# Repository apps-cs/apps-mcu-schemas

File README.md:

# K64F-KIT and Extension Modules

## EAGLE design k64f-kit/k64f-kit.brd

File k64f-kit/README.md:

# Base module K64F-KIT

The base module with ZIF sockets.

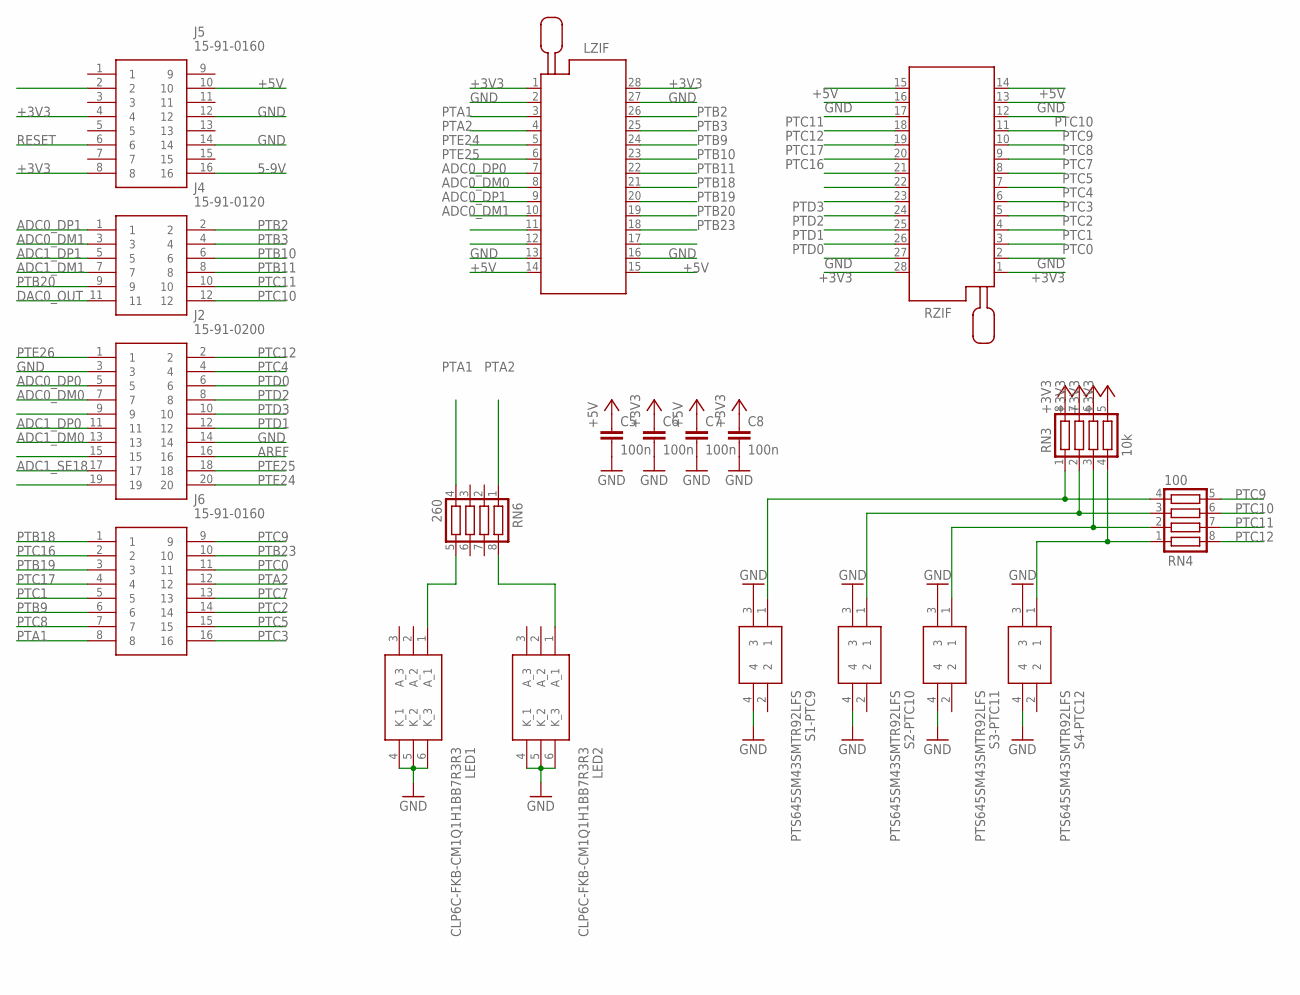
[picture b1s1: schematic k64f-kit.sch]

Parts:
C5, C6, C7, C8: 100n; C1206
J2: 15-91-0200; 15910200
J4: 15-91-0120; 15910120
J5, J6: 15-91-0160; 15910160
LED1, LED2: CLP6C-FKB-CM1Q1H1BB7R3R3; CLP6CFKBCM1Q1H1BB7R3R3
LZIF: 228-22-602; 228-1277-00-0602J
RN3: 10k; CTS742C083; FARNELL 1770137
RN4: 100; CTS742C083; FARNELL 1770131
RN6: 260; CTS742C083; FARNELL 2908182
RZIF: 228-22-602; 228-1277-00-0602J
S1-PTC9, S2-PTC10, S3-PTC11, S4-PTC12: PTS645SM43SMTR92LFS; PTS645(SMT); FARNELL 2320087

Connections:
5-9V: J5.16
+3V3: C6.1, C8.1, J5.4, J5.8, LZIF.1, LZIF.28, RN3.5, RN3.6, RN3.7, RN3.8, RZIF.1, RZIF.28
+5V: C5.1, C7.1, J5.10, LZIF.14, LZIF.15, RZIF.14, RZIF.15
ADC0_DM0: J2.7, LZIF.8
ADC0_DM1: J4.3, LZIF.10
ADC0_DP0: J2.5, LZIF.7
ADC0_DP1: J4.1, LZIF.9
ADC1_DM0: J2.13
ADC1_DM1: J4.7
ADC1_DP0: J2.11
ADC1_DP1: J4.5
ADC1_SE18: J2.17
AREF: J2.16
DAC0_OUT: J4.11
GND: C5.2, C6.2, C7.2, C8.2, J2.3, J2.14, J5.12, J5.14, LED1.4 (K_1), LED1.5 (K_2), LED1.6 (K_3), LED2.4 (K_1), LED2.5 (K_2), LED2.6 (K_3), LZIF.2, LZIF.13, LZIF.16, LZIF.27, RZIF.2, RZIF.13, RZIF.16, RZIF.27, S1-PTC9.3, S1-PTC9.4, S2-PTC10.3, S2-PTC10.4, S3-PTC11.3, S3-PTC11.4, S4-PTC12.3, S4-PTC12.4
unnamed: RN3.1, RN4.4, S1-PTC9.1
unnamed: RN3.2, RN4.3, S2-PTC10.1
unnamed: RN3.3, RN4.2, S3-PTC11.1
unnamed: RN3.4, RN4.1, S4-PTC12.1
unnamed: LED2.1 (A_1), RN6.8
unnamed: LED1.1 (A_1), RN6.5
PTA1: J6.8, LZIF.3, RN6.1
PTA2: J6.12, LZIF.4, RN6.4
PTB2: J4.2, LZIF.26
PTB3: J4.4, LZIF.25
PTB9: J6.6, LZIF.24
PTB10: J4.6, LZIF.23
PTB11: J4.8, LZIF.22
PTB18: J6.1, LZIF.21
PTB19: J6.3, LZIF.20
PTB20: J4.9, LZIF.19
PTB23: J6.10, LZIF.18
PTC0: J6.11, RZIF.3
PTC1: J6.5, RZIF.4
PTC2: J6.14, RZIF.5
PTC3: J6.16, RZIF.6
PTC4: J2.4, RZIF.7
PTC5: J6.15, RZIF.8
PTC7: J6.13, RZIF.9
PTC8: J6.7, RZIF.10
PTC9: J6.9, RN4.5, RZIF.11
PTC10: J4.12, RN4.6, RZIF.12
PTC11: J4.10, RN4.7, RZIF.17
PTC12: J2.2, RN4.8, RZIF.18
PTC16: J6.2, RZIF.20
PTC17: J6.4, RZIF.19
PTD0: J2.6, RZIF.26
PTD1: J2.12, RZIF.25
PTD2: J2.8, RZIF.24
PTD3: J2.10, RZIF.23
PTE24: J2.20, LZIF.5
PTE25: J2.18, LZIF.6
PTE26: J2.1
RESET: J5.6

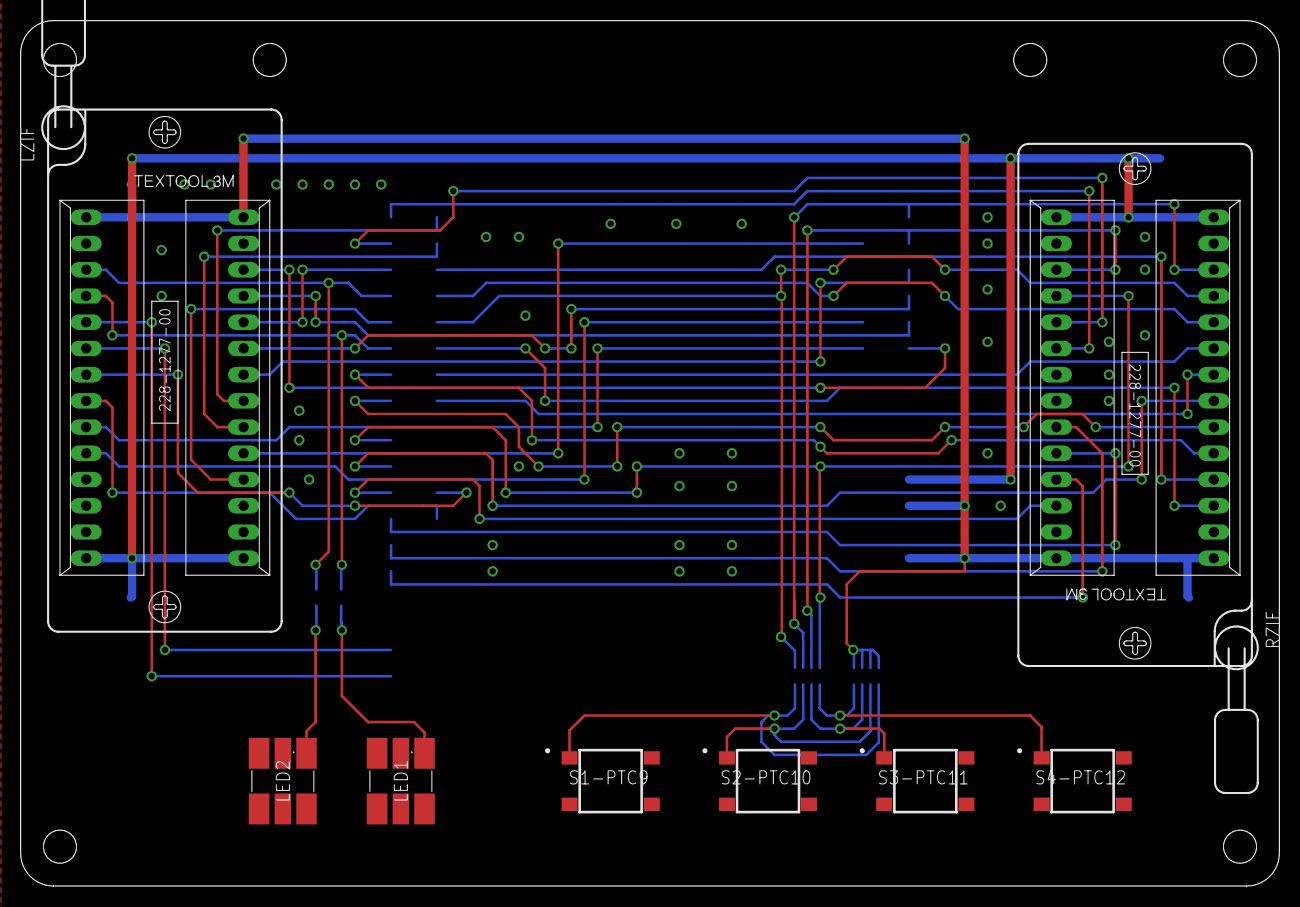
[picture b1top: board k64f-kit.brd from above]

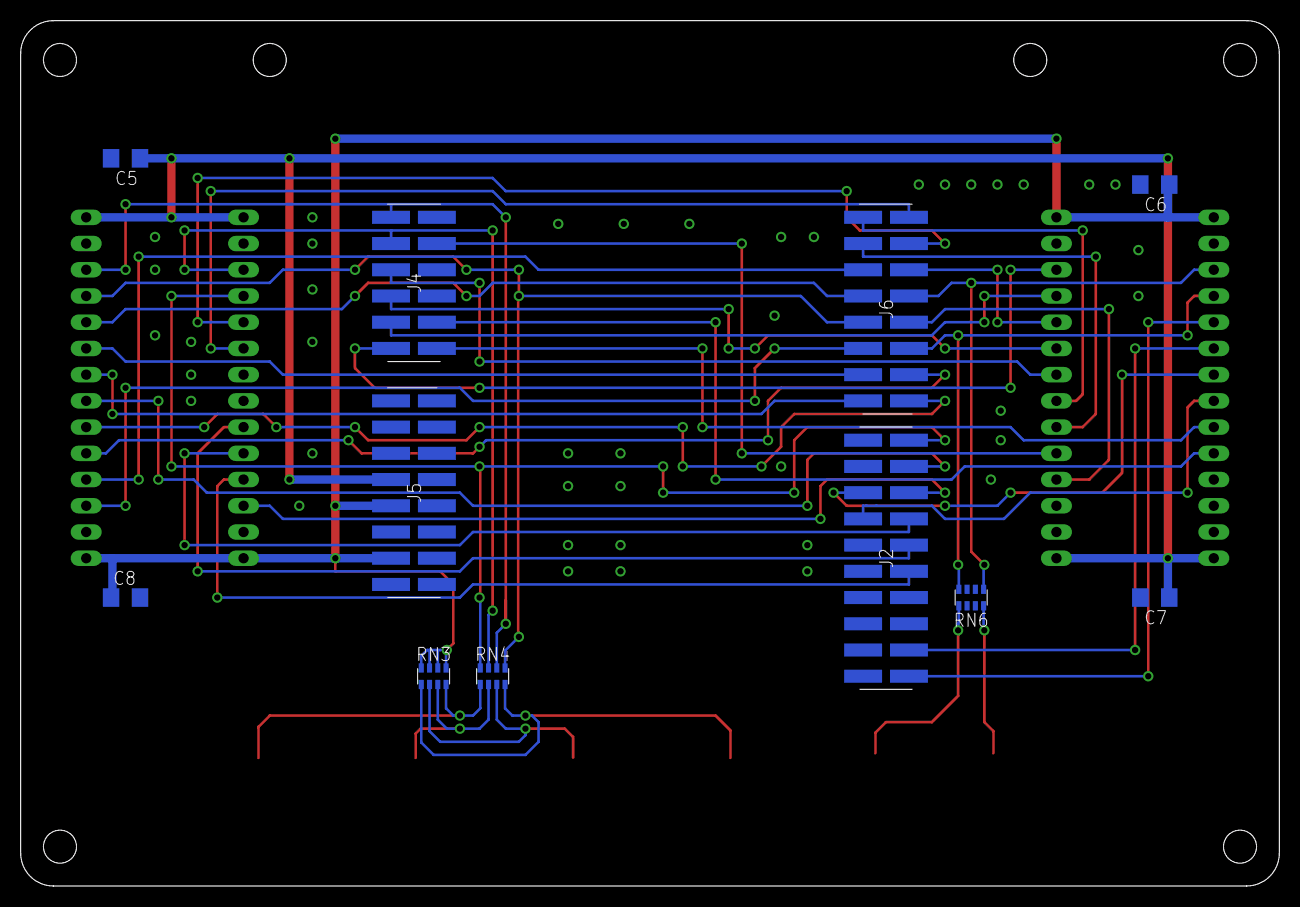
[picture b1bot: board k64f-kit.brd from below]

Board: 2 copper layers, 121.9 x 83.8 mm, 19 parts (11 on the bottom side), 44 nets.

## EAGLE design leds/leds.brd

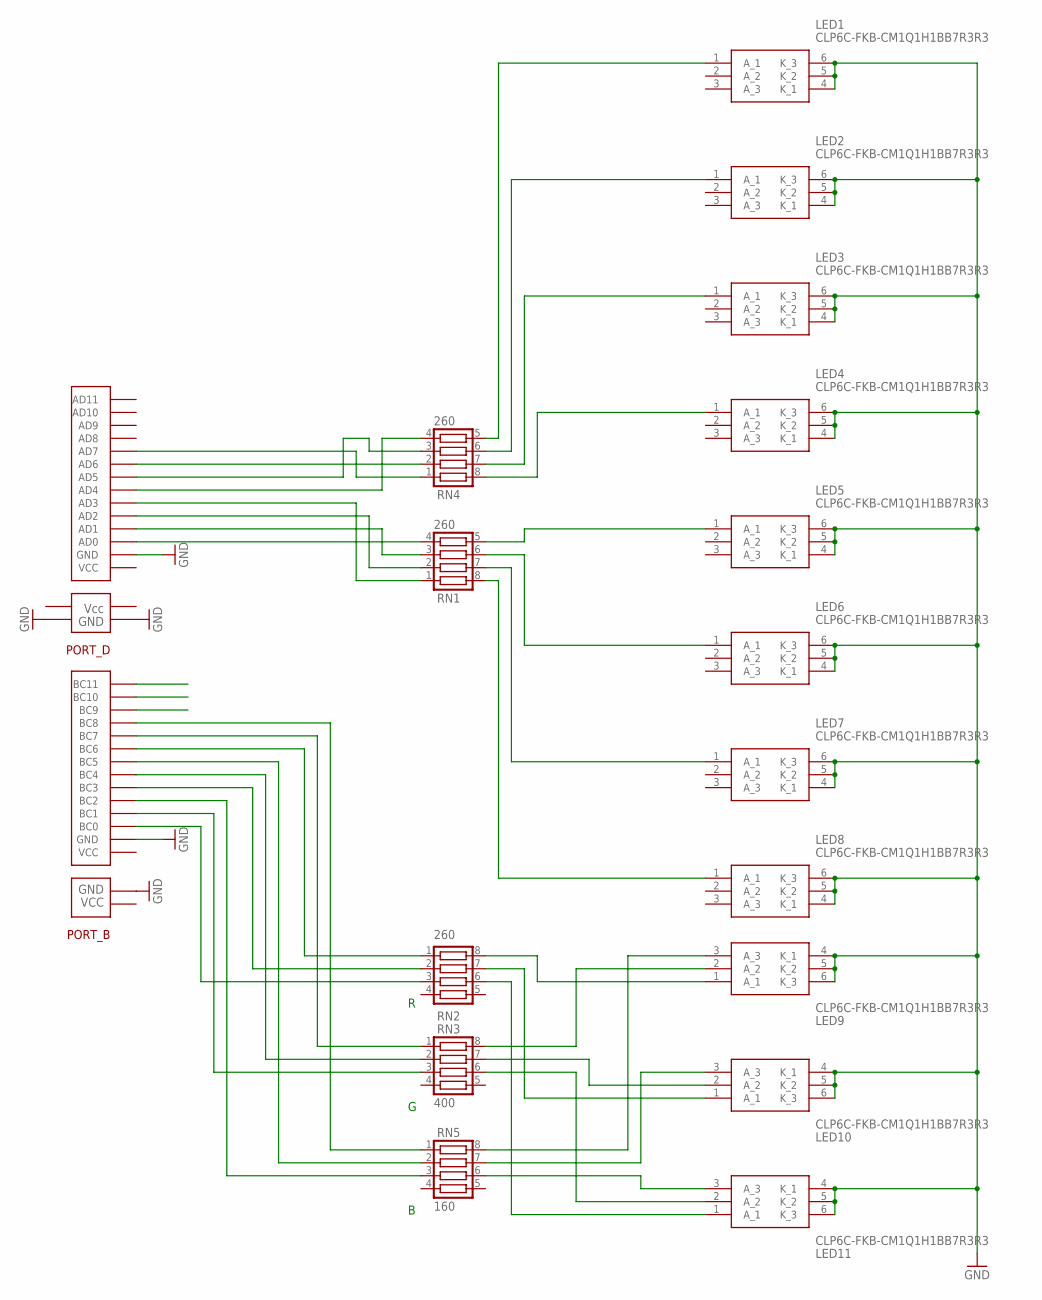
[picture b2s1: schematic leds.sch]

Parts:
LED1, LED2, LED3, LED4, LED5, LED6, LED7, LED8, LED9, LED10, LED11: CLP6C-FKB-CM1Q1H1BB7R3R3; CLP6CFKBCM1Q1H1BB7R3R3
PORT_B: PATICE_CERVENA
PORT_D: PATICE_ZELENA
RN1, RN2, RN4: 260; CTS742C083; FARNELL 2908182
RN3: 400; CTS742C083; FARNELL 2787792
RN5: 160; CTS742C083; FARNELL 2321721

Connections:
GND: LED1.4 (K_1), LED1.5 (K_2), LED1.6 (K_3), LED2.4 (K_1), LED2.5 (K_2), LED2.6 (K_3), LED3.4 (K_1), LED3.5 (K_2), LED3.6 (K_3), LED4.4 (K_1), LED4.5 (K_2), LED4.6 (K_3), LED5.4 (K_1), LED5.5 (K_2), LED5.6 (K_3), LED6.4 (K_1), LED6.5 (K_2), LED6.6 (K_3), LED7.4 (K_1), LED7.5 (K_2), LED7.6 (K_3), LED8.4 (K_1), LED8.5 (K_2), LED8.6 (K_3), LED9.4 (K_1), LED9.5 (K_2), LED9.6 (K_3), LED10.4 (K_1), LED10.5 (K_2), LED10.6 (K_3), LED11.4 (K_1), LED11.5 (K_2), LED11.6 (K_3), PORT_B.GND, PORT_B.GND/ (GND), PORT_D.GND, PORT_D.GND/ (GND), PORT_D.GND// (GND)
unnamed: LED1.1 (A_1), RN4.5
unnamed: LED2.1 (A_1), RN4.6
unnamed: LED3.1 (A_1), RN4.7
unnamed: LED4.1 (A_1), RN4.8
unnamed: PORT_B.CB3 (BC3), RN2.2
unnamed: PORT_B.CB0 (BC0), RN2.3
unnamed: LED7.1 (A_1), RN1.7
unnamed: LED9.2 (A_2), RN3.8
unnamed: LED8.1 (A_1), RN1.8
unnamed: PORT_D.AD0, RN1.4
unnamed: PORT_B.CB6 (BC6), RN2.1
unnamed: PORT_D.AD1, RN1.3
unnamed: PORT_B.CB2 (BC2), RN5.3
unnamed: PORT_D.AD2, RN1.2
unnamed: PORT_D.AD3, RN1.1
unnamed: PORT_D.AD7, RN4.1
unnamed: PORT_D.AD6, RN4.2
unnamed: PORT_D.AD5, RN4.3
unnamed: PORT_D.AD4, RN4.4
unnamed: LED5.1 (A_1), RN1.5
unnamed: PORT_B.CB1 (BC1), RN3.3
unnamed: PORT_B.CB7 (BC7), RN3.1
unnamed: LED6.1 (A_1), RN1.6
unnamed: PORT_B.CB8 (BC8), RN5.1
unnamed: PORT_B.CB5 (BC5), RN5.2
unnamed: PORT_B.CB4 (BC4), RN3.2
unnamed: LED9.3 (A_3), RN5.8
unnamed: LED10.3 (A_3), RN5.7
unnamed: LED11.3 (A_3), RN5.6
unnamed: LED9.1 (A_1), RN2.8
unnamed: LED10.1 (A_1), RN2.7
unnamed: LED11.1 (A_1), RN2.6
unnamed: LED11.2 (A_2), RN3.6
unnamed: LED10.2 (A_2), RN3.7

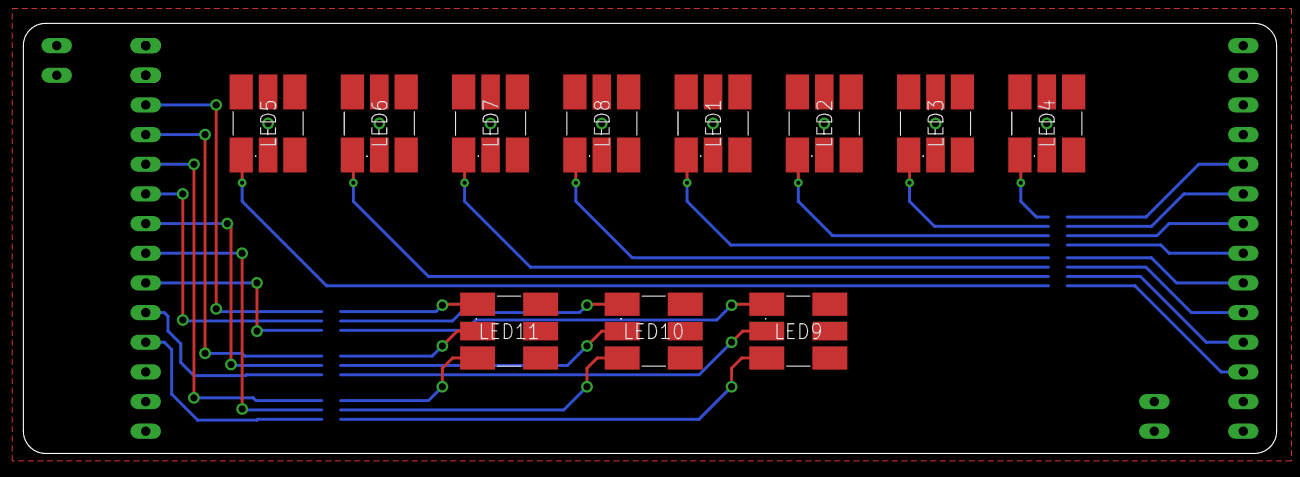
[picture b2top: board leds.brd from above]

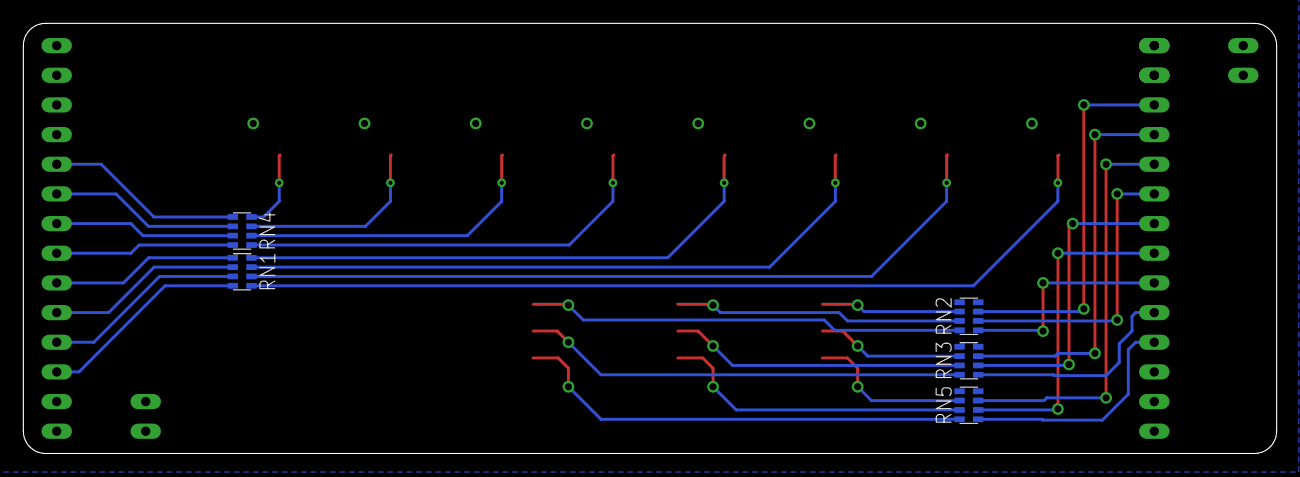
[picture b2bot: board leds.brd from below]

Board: 2 copper layers, 107.3 x 36.8 mm, 18 parts (5 on the bottom side), 35 nets.

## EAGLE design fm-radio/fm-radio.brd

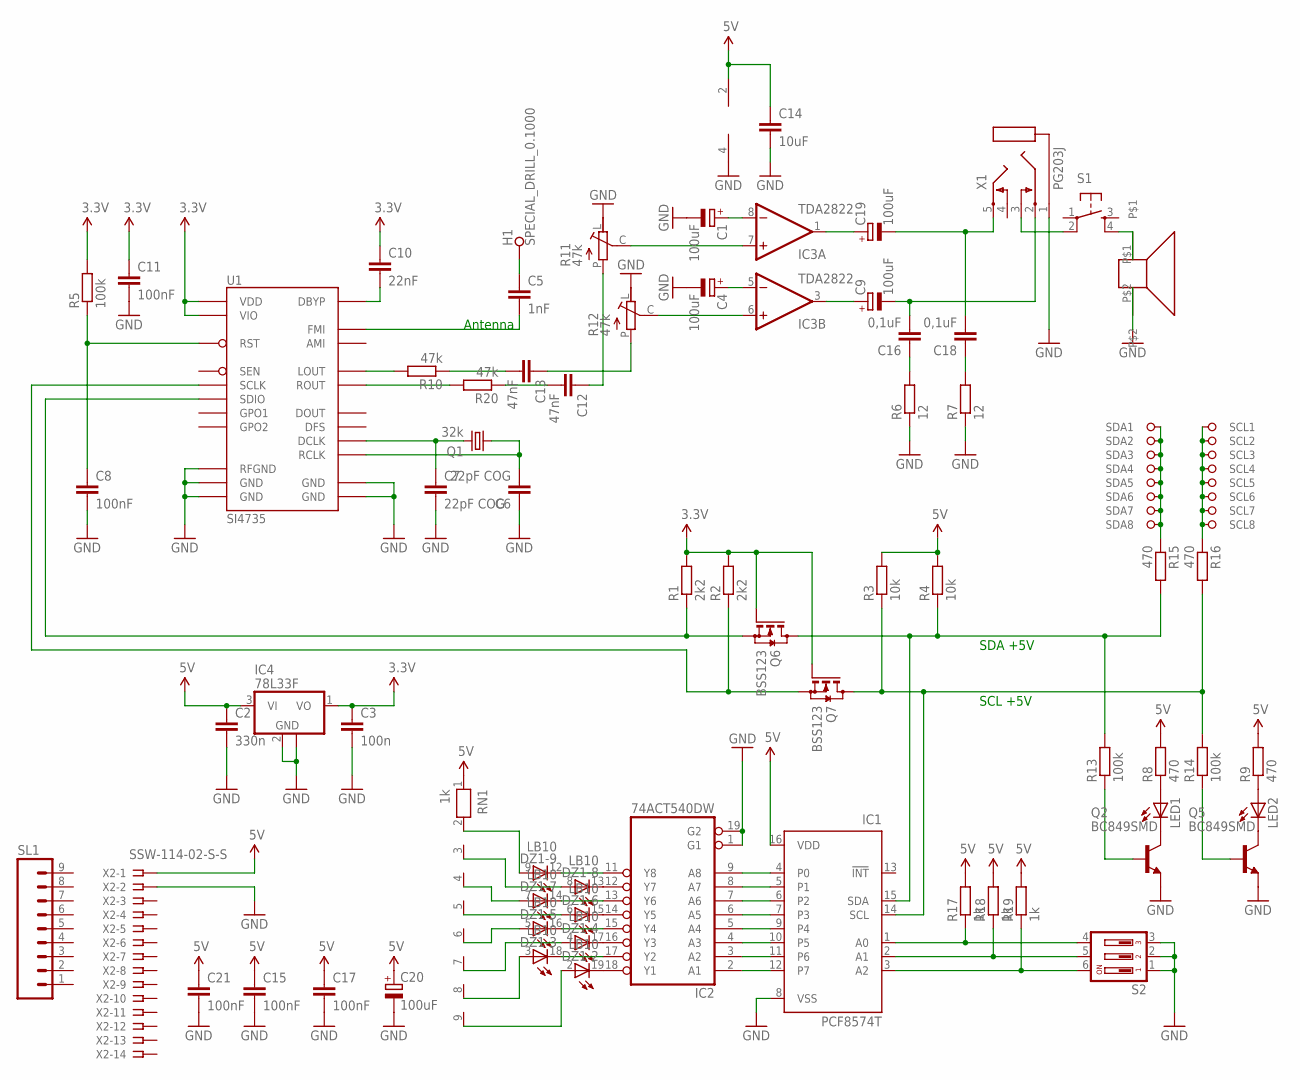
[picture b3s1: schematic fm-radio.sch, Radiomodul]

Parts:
C1, C4, C9, C19, C20: 100uF; CT3528
C2: 330n; C1206
C3: 100n; C1206
C5: 1nF; C1206
C6, C7: 22pF COG; C1206
C8, C11, C15, C17, C21: 100nF; C1206
C10: 22nF; C1206
C12, C13: 47nF; C1206
C14: 10uF; C1206
C16, C18: 0,1uF; C1206
DZ1: LB10
H1: SPECIAL_DRILL_0.1000; PAD_0.1000
IC1: PCF8574T; SO16W
IC2: 74ACT540DW; SO20W
IC3: TDA2822; SO08
IC4: 78L33F; SOT89
LED1, LED2: LEDCHIPLED_1206; CHIPLED_1206
Q1: 32k; MC-306
Q2, Q5: BC849SMD; SOT23-BEC
Q6, Q7: BSS123; SOT23
R1, R2: 2k2; R1206
R3, R4: 10k; R1206
R5, R13, R14: 100k; R1206
R6, R7: 12; R1206
R8, R9, R15, R16: 470; R1206
R10, R20: 47k; R1206
R11, R12: 47k; TRIMER
R17, R18, R19: 1k; R1206
RN1: 1k; RN-9
S1: TAC_SWITCHPTH; TACTILE-PTH
S2: DIP03YL
SL1: M09; 09P
U1: SI4735; SSOP24_NARROW
U$1: K23PC
U$7: PATICE_I2C
X1: PG203J
X2: SSW-114-02-S-S

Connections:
3.3V: C3.1, C10.1, C11.1, IC4.1 (VO), Q6.1 (G), Q7.1 (G), R1.2, R2.2, R5.2, U1.20 (VIO), U1.21 (VDD)
5V: C2.1, C14.1, C15.1, C17.1, C20.+, C21.1, IC1.16 (VDD), IC3.2 (V+), IC4.3 (VI), R3.2, R4.2, R8.2, R9.2, R17.2, R18.2, R19.2, RN1.1, X2.1
GND: C1.-, C2.2, C3.2, C4.-, C6.1, C7.2, C8.2, C11.2, C14.2, C15.2, C17.2, C20.-, C21.2, IC1.8 (VSS), IC2.1 (G1), IC2.10 (GND), IC2.19 (G2), IC3.4 (GND), IC4.2 (GND), IC4.2@1 (GND), Q2.E, Q5.E, R6.1, R7.1, R11.L, R12.L, S2.1, S2.2, S2.3, U1.9 (RFGND), U1.10 (GND), U1.11 (GND), U1.13 (GND), U1.14 (GND), U$1.P$2, X1.1, X2.2
unnamed: IC1.15 (SDA), Q6.3 (D), R4.1, R13.2, R15.2
unnamed: R16.1, U$7.SCL_1 (SCL1), U$7.SCL_2 (SCL2), U$7.SCL_3 (SCL3), U$7.SCL_4 (SCL4), U$7.SCL_5 (SCL5), U$7.SCL_6 (SCL6), U$7.SCL_7 (SCL7), U$7.SCL_8 (SCL8)
unnamed: Q7.2 (S), R2.1, U1.17 (SCLK)
unnamed: IC3.7 (+IN), R11.C
unnamed: Q6.2 (S), R1.1, U1.18 (SDIO)
unnamed: C5.2, U1.8 (FMI)
unnamed: C5.1, H1.1
unnamed: C7.1, Q1.4 (2), U1.3 (DCLK)
unnamed: C13.1, R12.P
unnamed: C8.1, R5.1, U1.15 (RST)
unnamed: S1.2, X1.3
unnamed: C1.+, IC3.8 (-IN)
unnamed: C6.2, Q1.1, U1.19 (RCLK)
unnamed: C10.2, U1.22 (DBYP)
unnamed: C12.1, R11.P
unnamed: S1.4, U$1.P$1
unnamed: C4.+, IC3.5 (-IN)
unnamed: IC3.6 (+IN), R12.C
unnamed: C16.1, R6.2
unnamed: C9.-, C16.2, X1.2
unnamed: C18.1, R7.2
unnamed: C18.2, C19.-, X1.5
unnamed: C19.+, IC3.1 (OUT)
unnamed: C9.+, IC3.3 (OUT)
unnamed: LED1.C, Q2.C
unnamed: LED2.C, Q5.C
unnamed: LED1.A, R8.1
unnamed: LED2.A, R9.1
unnamed: Q2.B, R13.1
unnamed: Q5.B, R14.1
unnamed: R15.1, U$7.SDA_1 (SDA1), U$7.SDA_2 (SDA2), U$7.SDA_3 (SDA3), U$7.SDA_4 (SDA4), U$7.SDA_5 (SDA5), U$7.SDA_6 (SDA6), U$7.SDA_7 (SDA7), U$7.SDA_8 (SDA8)
unnamed: IC1.14 (SCL), Q7.3 (D), R3.1, R14.2, R16.2
unnamed: IC1.4 (P0), IC2.9 (A8)
unnamed: IC1.12 (P7), IC2.2 (A1)
unnamed: IC1.11 (P6), IC2.3 (A2)
unnamed: IC1.10 (P5), IC2.4 (A3)
unnamed: IC1.9 (P4), IC2.5 (A4)
unnamed: IC1.7 (P3), IC2.6 (A5)
unnamed: IC1.6 (P2), IC2.7 (A6)
unnamed: IC1.5 (P1), IC2.8 (A7)
unnamed: DZ1.12 (C), IC2.11 (Y8)
unnamed: DZ1.13 (C), IC2.12 (Y7)
unnamed: DZ1.14 (C), IC2.13 (Y6)
unnamed: DZ1.15 (C), IC2.14 (Y5)
unnamed: DZ1.16 (C), IC2.15 (Y4)
unnamed: DZ1.17 (C), IC2.16 (Y3)
unnamed: DZ1.18 (C), IC2.17 (Y2)
unnamed: DZ1.19 (C), IC2.18 (Y1)
unnamed: DZ1.9 (A), RN1.2
unnamed: DZ1.8 (A), RN1.3
unnamed: DZ1.7 (A), RN1.4
unnamed: DZ1.6 (A), RN1.5
unnamed: DZ1.5 (A), RN1.6
unnamed: DZ1.4 (A), RN1.7
unnamed: DZ1.3 (A), RN1.8
unnamed: DZ1.2 (A), RN1.9
unnamed: IC1.1 (A0), R17.1, S2.4
unnamed: IC1.2 (A1), R18.1, S2.5
unnamed: IC1.3 (A2), R19.1, S2.6
unnamed: R10.2, U1.24 (LOUT)
unnamed: C12.2, R20.1
unnamed: C13.2, R10.1
unnamed: R20.2, U1.23 (ROUT)
VCC: IC2.20 (VCC)

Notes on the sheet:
SDA +5V
SCL +5V
Antenna

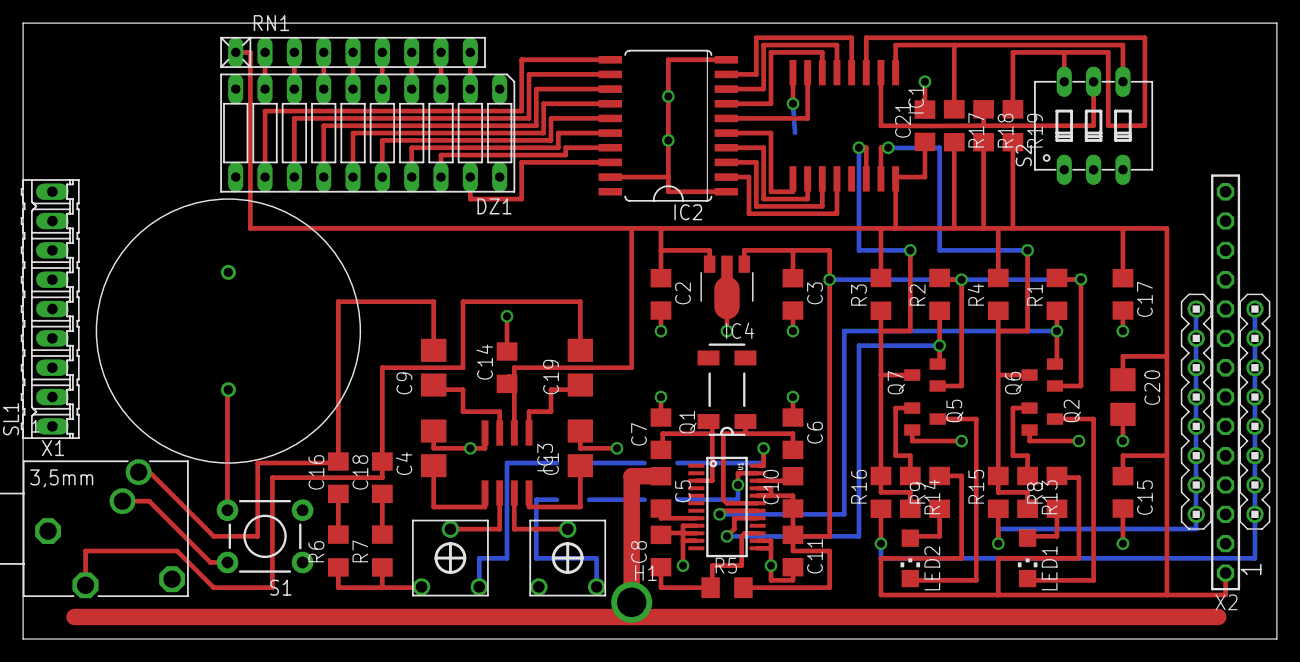
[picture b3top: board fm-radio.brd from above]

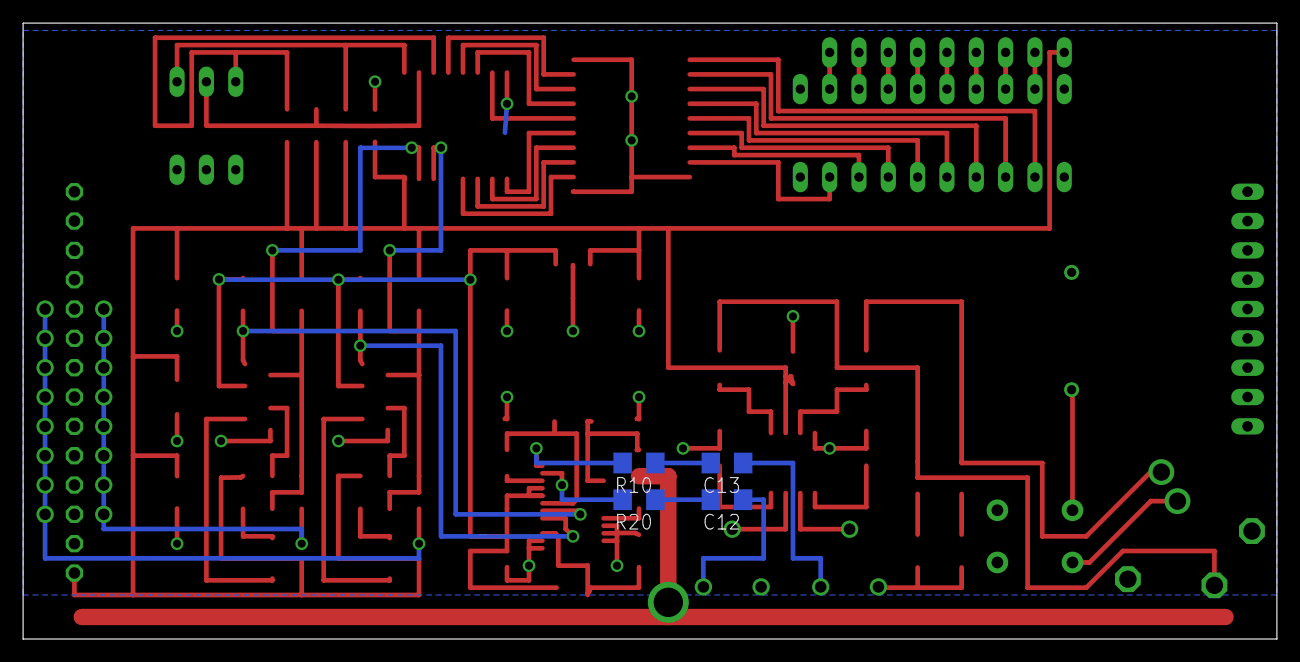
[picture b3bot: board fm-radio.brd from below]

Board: 2 copper layers, 108.6 x 53.3 mm, 63 parts (4 on the bottom side), 66 nets.

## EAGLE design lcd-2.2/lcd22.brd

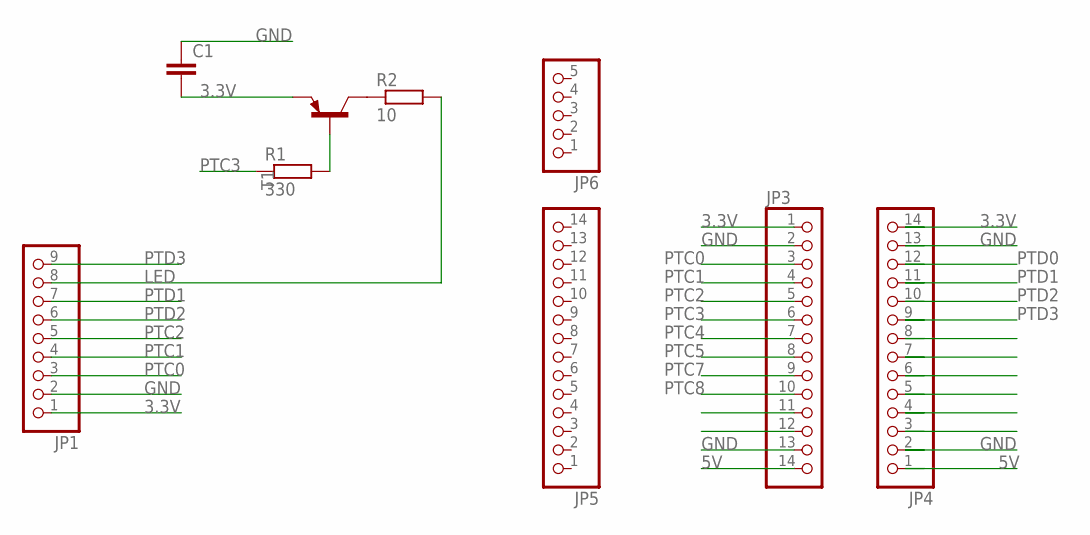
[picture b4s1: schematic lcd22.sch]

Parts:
C1: C-EU025-025X050; C025-025X050
JP1: PINHD-1X9; 1X09
JP3, JP4, JP5: PINHD-1X14; 1X14
JP6: PINHD-1X5; 1X05
R1: 330; 0207/10
R2: 10; 0207/10
T1: BC557C-PNP-TO92-EBC; TO92-EBC

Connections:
3.3V: C1.2, JP1.1, JP3.1, JP4.14, T1.E
5V: JP3.14, JP4.1
GND: C1.1, JP1.2, JP3.2, JP3.13, JP4.2, JP4.13
LED: JP1.8, R2.2
unnamed: R1.2, T1.B
unnamed: R2.1, T1.C
PTC0: JP1.3, JP3.3
PTC1: JP1.4, JP3.4
PTC2: JP1.5, JP3.5
PTC3: JP3.6, R1.1
PTC4: JP3.7
PTC5: JP3.8
PTC7: JP3.9
PTC8: JP3.10
PTD0: JP4.12
PTD1: JP1.7, JP4.11
PTD2: JP1.6, JP4.10
PTD3: JP1.9, JP4.9

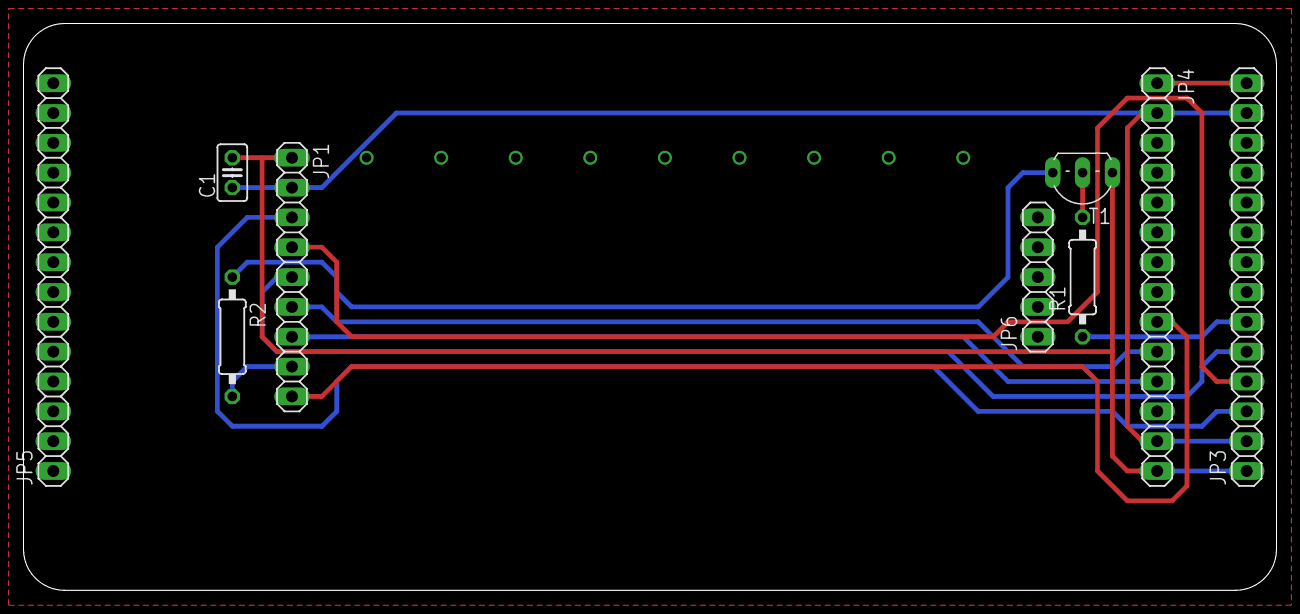
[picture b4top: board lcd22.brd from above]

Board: 2 copper layers, 106.7 x 48.3 mm, 9 parts (0 on the bottom side), 13 nets.

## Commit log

2021-01-29 The first commit
2021-01-29 The base module added
2021-01-29 Extension modules added
2021-01-29 K64F-KIT brd update

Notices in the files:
parts and their libraries:
SparkFun: Licensing: CC v3.0 Share-Alike You are welcome to use this library for commercial purposes.
